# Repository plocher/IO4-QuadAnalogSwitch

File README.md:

# IO4-QuadAnalogSwitch
## License: CERN Open Hardware Licence v1.2

Quad Analog switch - 16 inputs to 4 A/D lines

An ESP32 only has 4x usable A/D lines when WiFi is also used.
This board is a multiplexor for 4 banks of 4 analog inputs to those A/D lines.

The initial use case is to support a preset controller for LED layout lighting
that has R,G,B and W levels for Background horizon, background sky, foreground sky and suplementary lighting.
(that is, 4 banks of 4 linear potentiometers each...)

Usage:

Set the digital outputs to select the desired bank:

    D C B A  
    X 0 1 1	Bank A  
    X 0 0 1	Bank B  
    X 1 0 0	Bank C  
    X 0 0 0	Bank D    

(output "D" controls a diagnostic LED on the board)

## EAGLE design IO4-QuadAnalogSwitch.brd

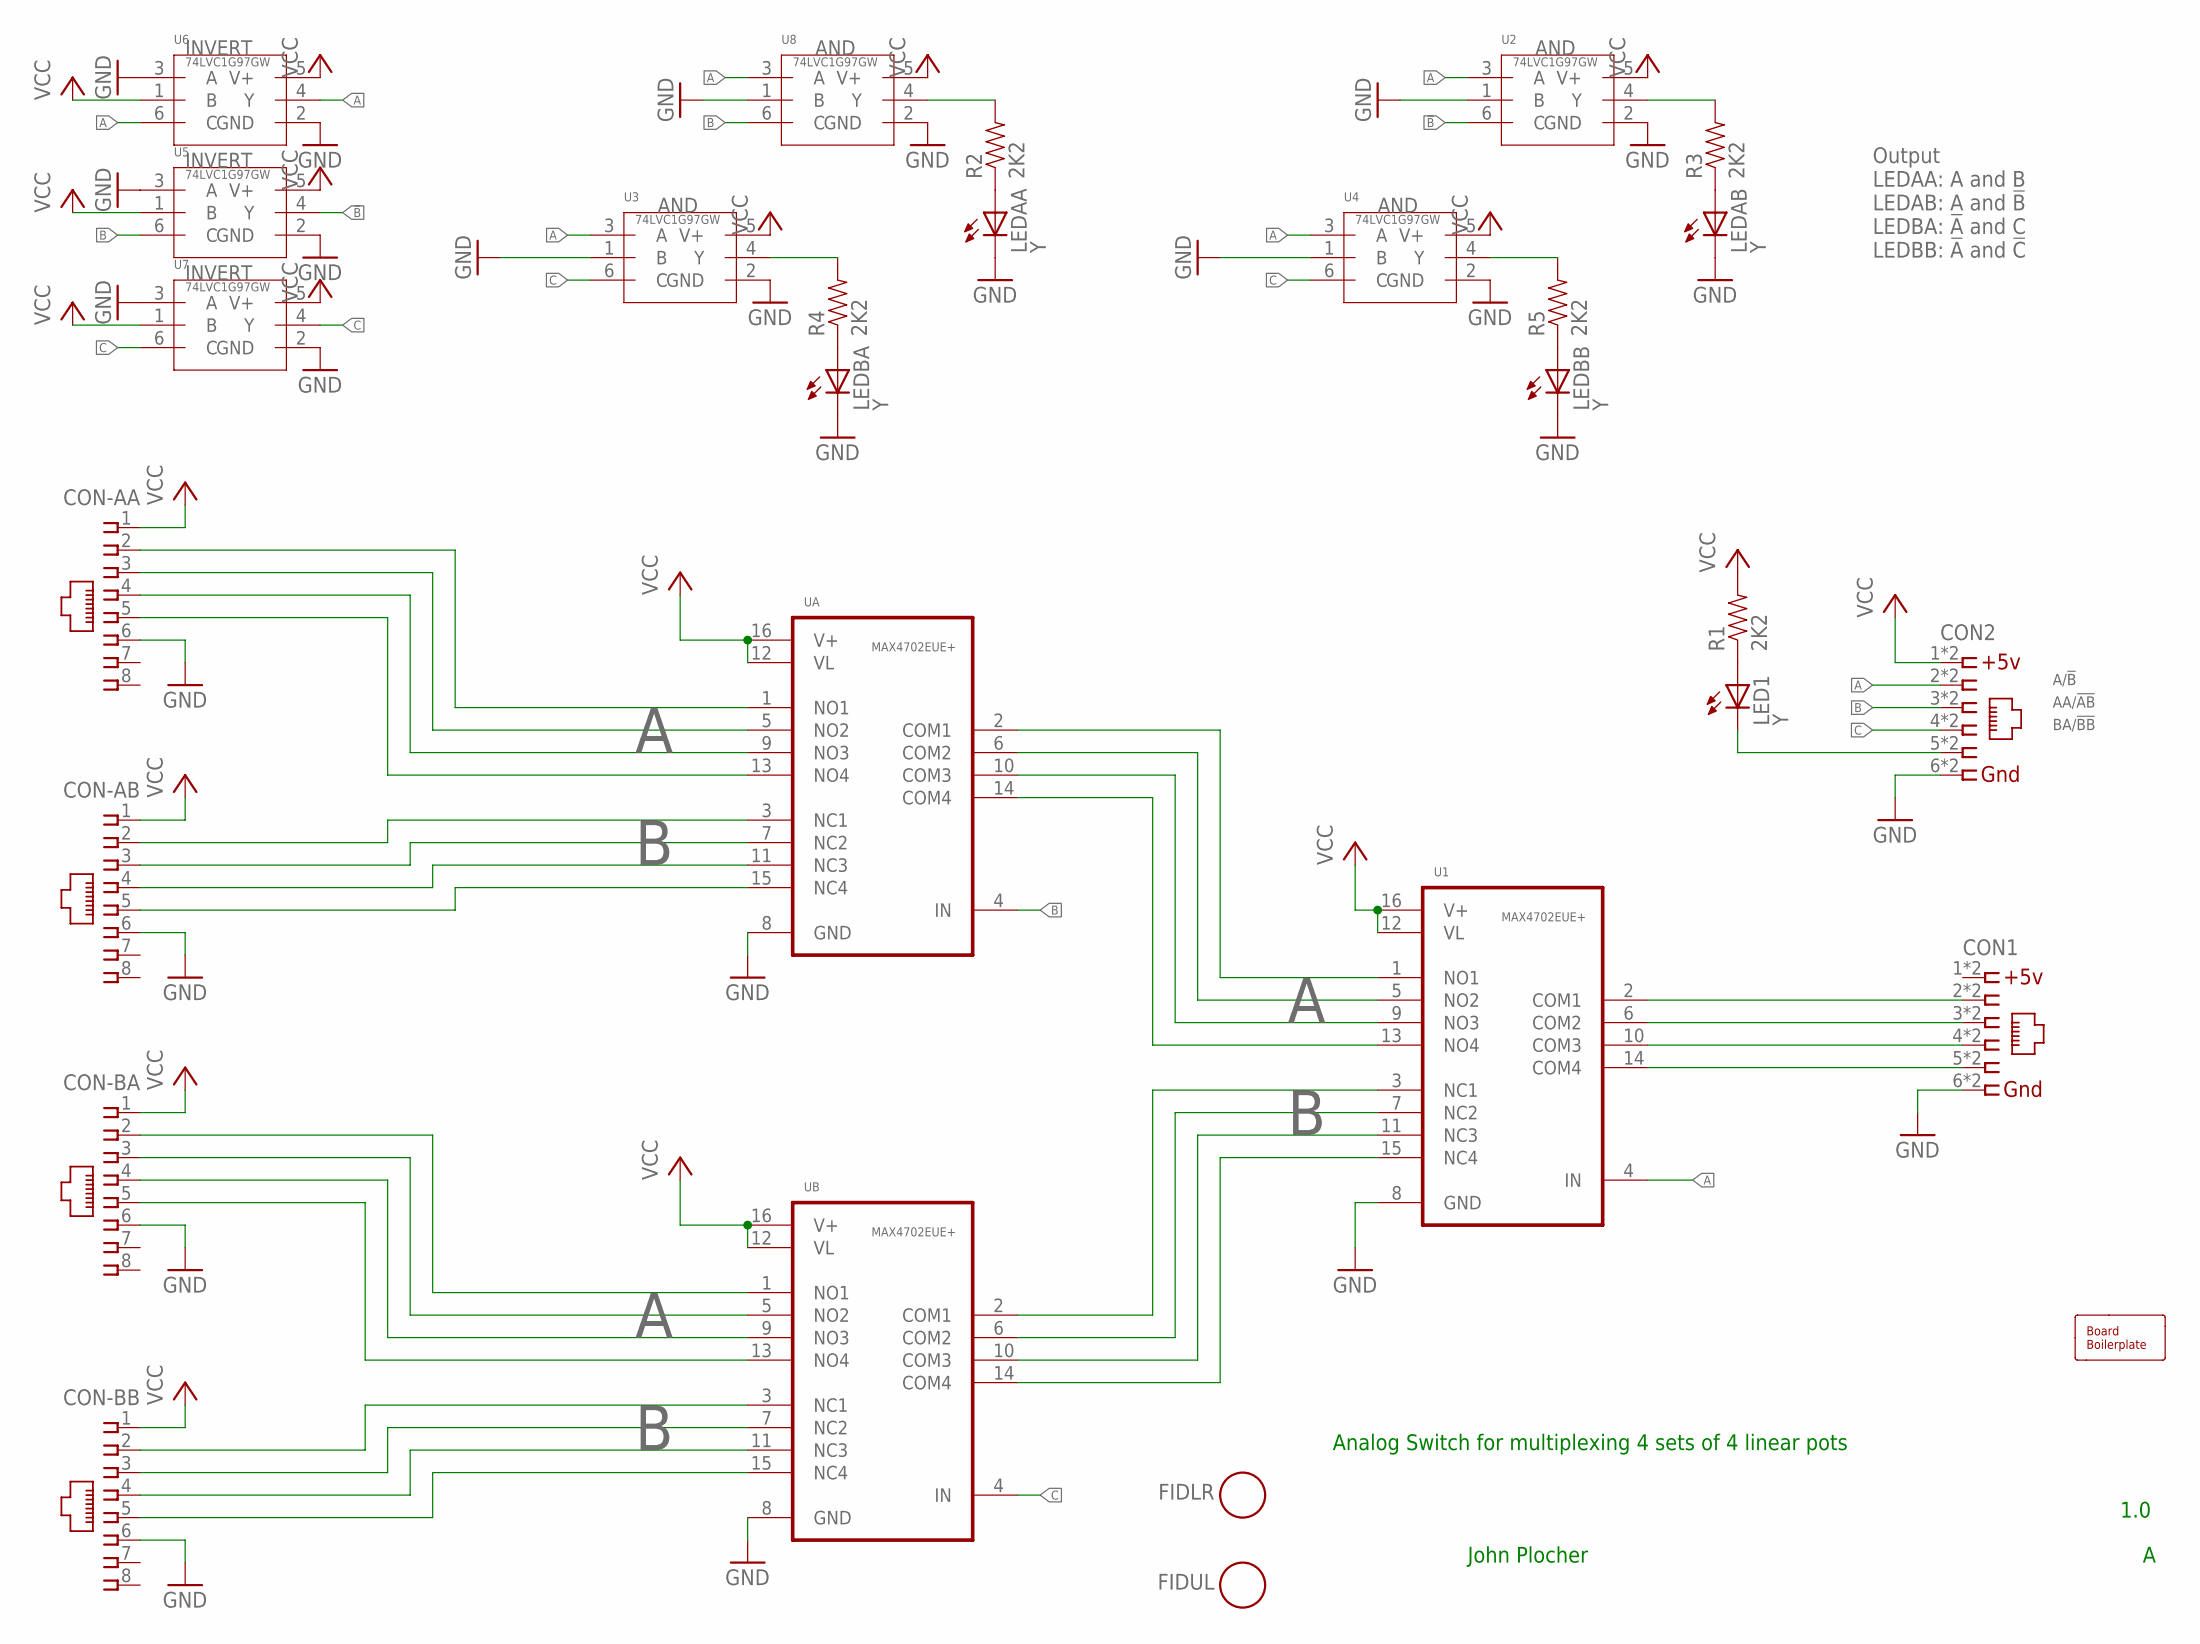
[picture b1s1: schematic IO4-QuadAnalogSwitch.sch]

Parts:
BOARD1: BOARD80X100; BOARD-DINRAIL-3.17INX10CM
CON1, CON2: CONNECTOR-IO4IPINS; RJ24-INVERTED-PINS
CON-AA: CONNECTOR-RJ45-FRONT; RJ45-NO-SHIELD
CON-AB: CONNECTOR-RJ45-FRONT; RJ45-NO-SHIELD
CON-BA: CONNECTOR-RJ45-FRONT; RJ45-NO-SHIELD
CON-BB: CONNECTOR-RJ45-FRONT; RJ45-NO-SHIELD
FIDLR: FIDUCIAL; FIDUCIAL_1MM
FIDUL: FIDUCIAL; FIDUCIAL_1MM
LED1: Y; 0603-LED
LEDAA: Y; 0603-LED
LEDAB: Y; 0603-LED
LEDBA: Y; 0603-LED
LEDBB: Y; 0603-LED
R1, R2, R3, R4, R5: 2K2; 0603-RES
U1: MAX4702EUE+
U2, U3, U4, U5, U6, U7, U8: 74LVC1G97GW; SOT363
UA: MAX4702EUE+
UB: MAX4702EUE+

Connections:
1: CON1.1, CON1.1@1 (1)
!A: U3.3 (A), U4.3 (A), U6.4 (Y)
!B: U2.6 (C), U5.4 (Y)
!C: U4.6 (C), U7.4 (Y)
A: CON2.2, CON2.2@1 (2), U1.4 (IN), U2.3 (A), U6.6 (C), U8.3 (A)
A1: U1.1 (NO1), UA.2 (COM1)
A2: U1.5 (NO2), UA.6 (COM2)
A3: U1.9 (NO3), UA.10 (COM3)
A4: U1.13 (NO4), UA.14 (COM4)
AA1: CON-AA.2, UA.1 (NO1)
AA2: CON-AA.3, UA.5 (NO2)
AA3: CON-AA.4, UA.9 (NO3)
AA4: CON-AA.5, UA.13 (NO4)
AB1: CON-AB.2, UA.3 (NC1)
AB2: CON-AB.3, UA.7 (NC2)
AB3: CON-AB.4, UA.11 (NC3)
AB4: CON-AB.5, UA.15 (NC4)
B: CON2.3, CON2.3@1 (3), U5.6 (C), U8.6 (C), UA.4 (IN)
B1: U1.3 (NC1), UB.2 (COM1)
B2: U1.7 (NC2), UB.6 (COM2)
B3: U1.11 (NC3), UB.10 (COM3)
B4: U1.15 (NC4), UB.14 (COM4)
BA1: CON-BA.2, UB.1 (NO1)
BA2: CON-BA.3, UB.5 (NO2)
BA3: CON-BA.4, UB.9 (NO3)
BA4: CON-BA.5, UB.13 (NO4)
BB1: CON-BB.2, UB.3 (NC1)
BB2: CON-BB.3, UB.7 (NC2)
BB3: CON-BB.4, UB.11 (NC3)
BB4: CON-BB.5, UB.15 (NC4)
C: CON2.4, CON2.4@1 (4), U3.6 (C), U7.6 (C), UB.4 (IN)
COM1: CON1.2, CON1.2@1 (2), U1.2 (COM1)
COM2: CON1.3, CON1.3@1 (3), U1.6 (COM2)
COM3: CON1.4, CON1.4@1 (4), U1.10 (COM3)
COM4: CON1.5, CON1.5@1 (5), U1.14 (COM4)
GND: CON1.6, CON1.6@1 (6), CON2.6, CON2.6@1 (6), CON-AA.6, CON-AB.6, CON-BA.6, CON-BB.6, LEDAA.C, LEDAB.C, LEDBA.C, LEDBB.C, U1.8 (GND), U2.1 (B), U2.2 (GND), U3.1 (B), U3.2 (GND), U4.1 (B), U4.2 (GND), U5.2 (GND), U5.3 (A), U6.2 (GND), U6.3 (A), U7.2 (GND), U7.3 (A), U8.1 (B), U8.2 (GND), UA.8 (GND), UB.8 (GND)
unnamed: LED1.A, R1.1
unnamed: CON2.5, CON2.5@1 (5), LED1.C
unnamed: LEDAA.A, R2.1
unnamed: LEDBB.A, R5.1
unnamed: LEDAB.A, R3.1
unnamed: R2.2, U8.4 (Y)
unnamed: LEDBA.A, R4.1
unnamed: R5.2, U4.4 (Y)
unnamed: R4.2, U3.4 (Y)
unnamed: R3.2, U2.4 (Y)
VCC: CON2.1, CON2.1@1 (1), CON-AA.1, CON-AB.1, CON-BA.1, CON-BB.1, R1.2, U1.12 (VL), U1.16 (V+), U2.5 (V+), U3.5 (V+), U4.5 (V+), U5.1 (B), U5.5 (V+), U6.1 (B), U6.5 (V+), U7.1 (B), U7.5 (V+), U8.5 (V+), UA.12 (VL), UA.16 (V+), UB.12 (VL), UB.16 (V+)

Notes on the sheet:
Analog Switch for multiplexing 4 sets of 4 linear pots
1.0
John Plocher
AND
INVERT
A/!B
AA/!AB
BA/!BB
Output LEDAA: A and B LEDAB: A and !B! LEDBA: !A! and C LEDBB: !A! and !C!

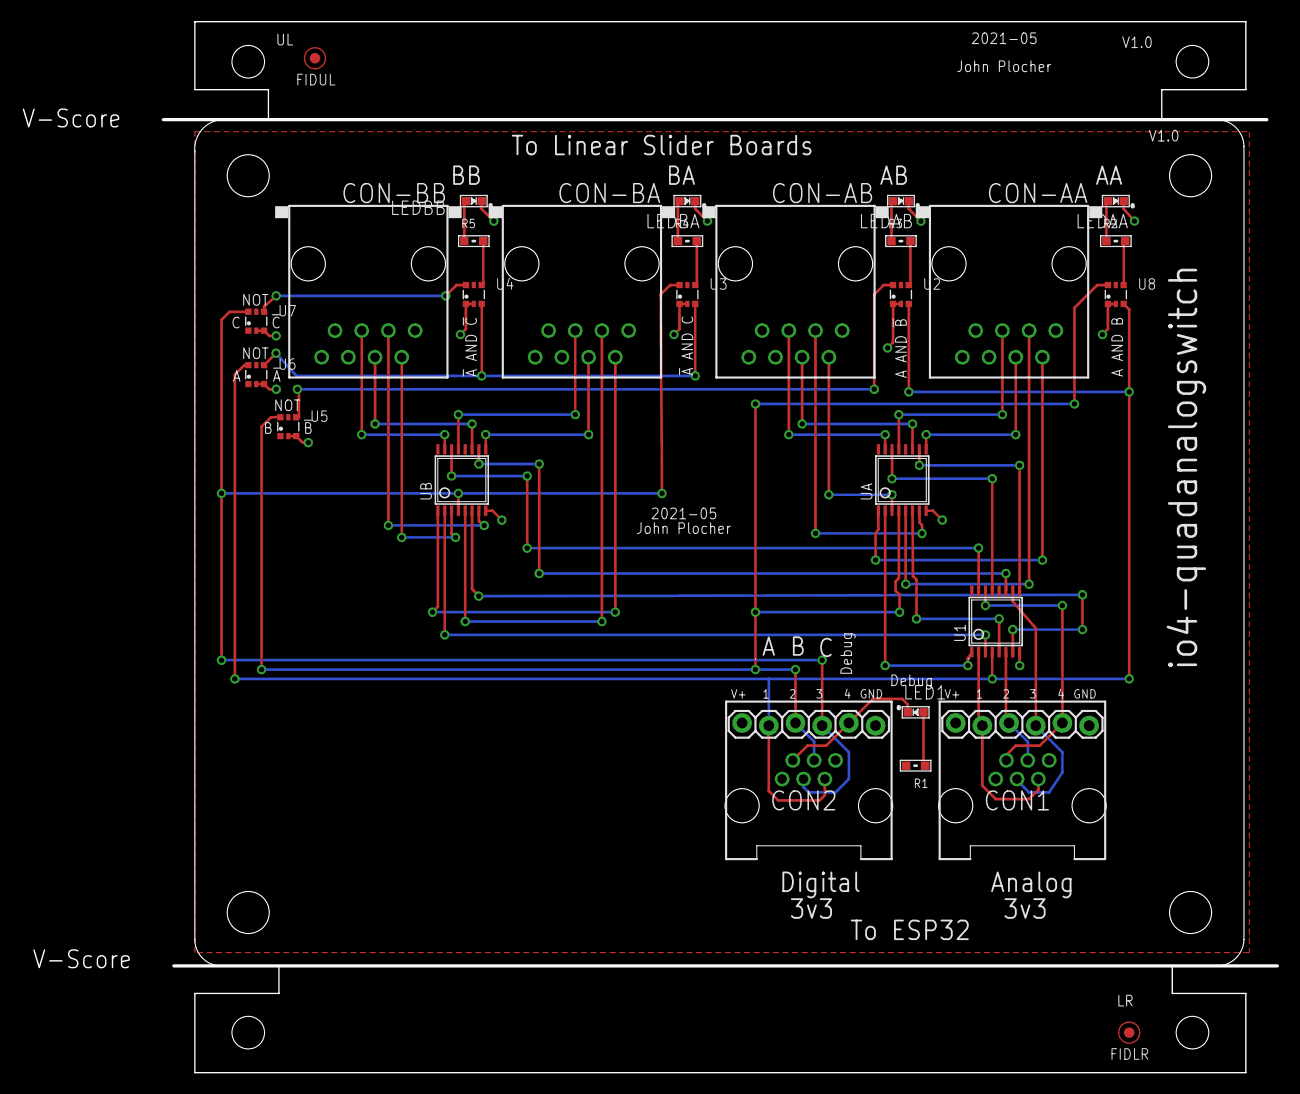
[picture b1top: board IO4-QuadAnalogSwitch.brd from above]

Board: 2 copper layers, 106.0 x 100.0 mm, 29 parts (0 on the bottom side), 47 nets.

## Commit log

2021-06-03 Initial version
2021-06-03 fixed docs
2021-06-03 markdown fix
2021-06-03 missed tiny airwire
